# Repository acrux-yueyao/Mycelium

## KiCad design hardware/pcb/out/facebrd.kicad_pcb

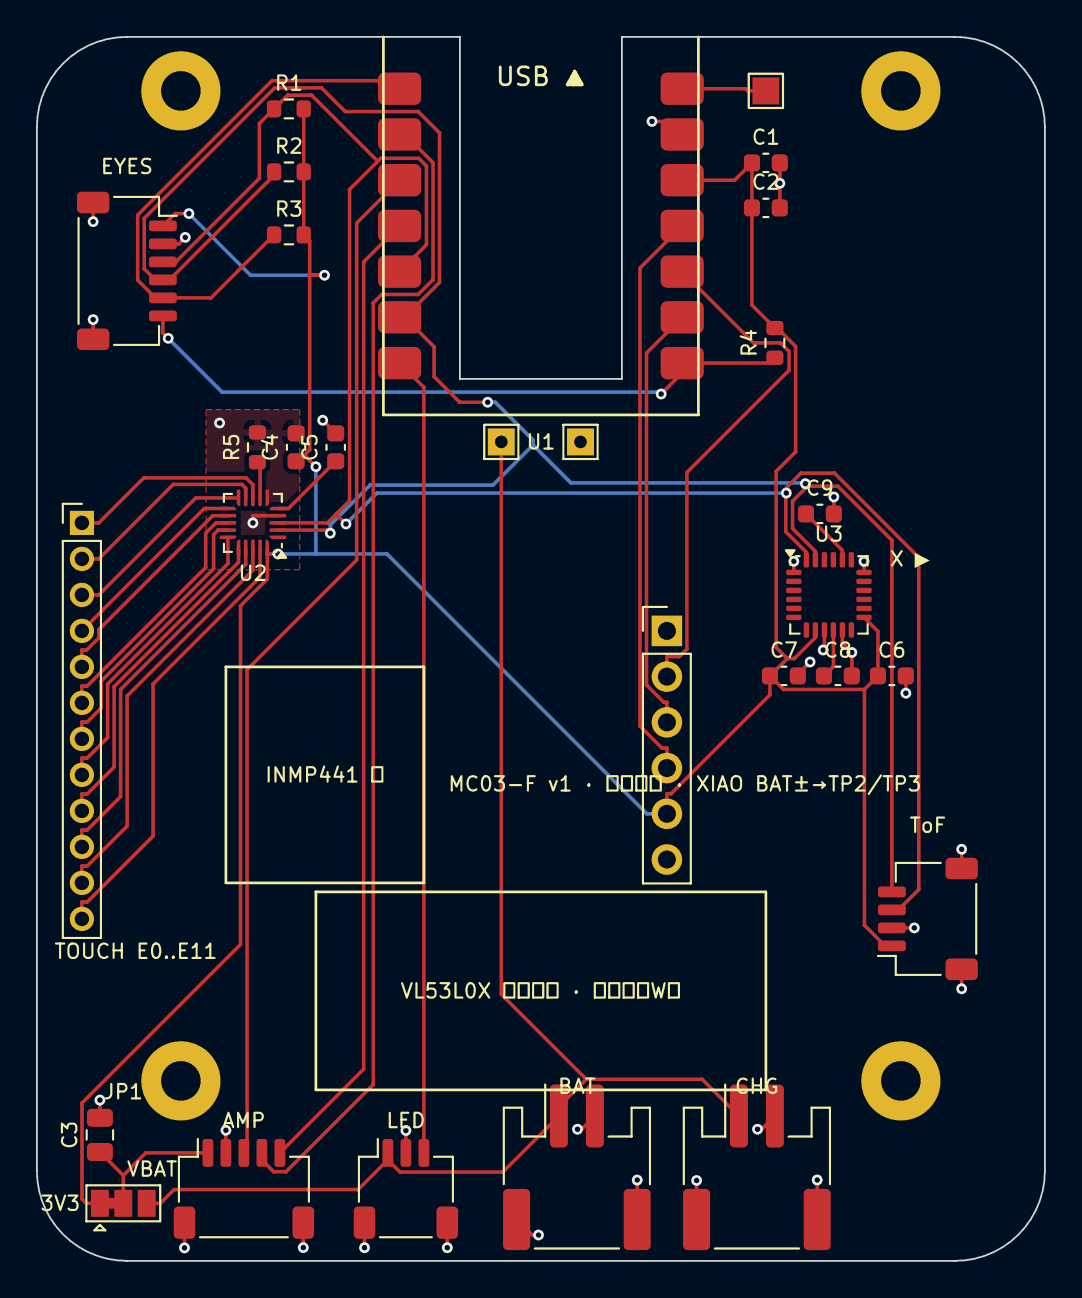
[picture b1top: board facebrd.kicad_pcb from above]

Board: 2 copper layers, 56.0 x 68.0 mm, 33 parts (0 on the bottom side), 32 nets.

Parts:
C1: 10uF; C_0603_1608Metric
C2, C4, C5, C6, C8: 100nF; C_0603_1608Metric
C3: 22uF; C_0805_2012Metric
C7: 10nF; C_0603_1608Metric
C9: 2.2nF; C_0603_1608Metric
H1, H2, H3, H4: M2; MountingHole_2.2mm_M2_Pad
J1: ToF 4P; JST_SH_SM04B-SRSS-TB_1x04-1MP_P1.00mm_Horizontal
J2: MIC pads; PinHeader_1x06_P2.54mm_Vertical
J3: EYES 6P; JST_SH_SM06B-SRSS-TB_1x06-1MP_P1.00mm_Horizontal
J4: BAT; JST_PH_S2B-PH-SM4-TB_1x02-1MP_P2.00mm_Horizontal
J5: LED 3P; JST_SH_SM03B-SRSS-TB_1x03-1MP_P1.00mm_Horizontal
J6: AMP 5P; JST_SH_SM05B-SRSS-TB_1x05-1MP_P1.00mm_Horizontal
J7: TOUCH pads; PinHeader_1x12_P2.00mm_Vertical
J8: CHG; JST_PH_S2B-PH-SM4-TB_1x02-1MP_P2.00mm_Horizontal
JP1: AMP_VIN sel; SolderJumper-3_P1.3mm_Bridged12_Pad1.0x1.5mm
R1, R2, R3, R4: 4.7k; R_0603_1608Metric
R5: 75k; R_0603_1608Metric
TP1: VBUS; TestPoint_Pad_1.5x1.5mm
TP2: BAT+; TestPoint_THTPad_1.5x1.5mm_Drill0.7mm
TP3: BAT-; TestPoint_THTPad_1.5x1.5mm_Drill0.7mm
U1: XIAO-ESP32S3; XIAO-ESP32S3_SMD
U2: MPR121QR2; UQFN-20_3x3mm_P0.4mm
U3: MPU-6050; InvenSense_QFN-24_4x4mm_P0.5mm

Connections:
3V3: C1.1, C2.1, C4.1, C6.1, C7.1, J1.1, J2.5, J3.1, JP1.1, R1.2, R2.2, R3.2, R4.2, U1.12, U2.20, U3.8, U3.13
AMP_VIN: C3.1, J6.1, JP1.2
CPOUT: C9.1, U3.20
ELE0: J7.1, U2.8
ELE1: J7.2, U2.9
ELE2: J7.3, U2.10
ELE3: J7.4, U2.11
ELE4: J7.5, U2.12
ELE5: J7.6, U2.13
ELE6: J7.7, U2.14
ELE7: J7.8, U2.15
ELE8: J7.9, U2.16
ELE9: J7.10, U2.17
ELE10: J7.11, U2.18
ELE11: J7.12, U2.19
GND: C1.2, C2.2, C3.2, C4.2, C5.2, C6.2, C7.2, C8.2, C9.2, H1.1, H2.1, H3.1, H4.1, J1.2, J1.MP, J2.1, J2.6, J3.2, J3.MP, J4.2, J4.MP, J5.2, J5.MP, J6.2, J6.MP, J8.2, J8.MP, R5.2, TP3.1, U1.13, U2.4, U2.6, U3.1, U3.9, U3.11, U3.18
I2S_BCLK: J6.3, U1.3
I2S_DIN: J6.5, U1.4
I2S_LRC: J6.4, U1.2
LED_DIN: J5.3, U1.7
MIC_SCK: J2.3, U1.9
MIC_SD: J2.4, U1.11
MIC_WS: J2.2, U1.10
REGOUT: C8.1, U3.10
REXT: R5.1, U2.7
SCL0: J1.4, J3.4, R2.1, U1.6, U2.2, U3.23
SCL1: J3.6, R4.1, U1.8
SDA0: J1.3, J3.3, R1.1, U1.5, U2.3, U3.24
SDA1: J3.5, R3.1, U1.1
VBAT: J4.1, J5.1, J8.1, JP1.3, TP2.1
VBUS: TP1.1, U1.14
VREG: C5.1, U2.5

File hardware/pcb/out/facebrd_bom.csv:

Comment,Designator,Footprint,LCSC Part #
MPR121QR2,U2,UQFN-20_3x3mm_P0.4mm,C91322
MPU-6050,U3,InvenSense_QFN-24_4x4mm_P0.5mm,C24112
10uF,C1,C_0603_1608Metric,C19702
100nF,"C2,C4,C5,C6,C8",C_0603_1608Metric,C14663
22uF,C3,C_0805_2012Metric,C45783
75k,R5,R_0603_1608Metric,C18671
10nF,C7,C_0603_1608Metric,C57112
2.2nF,C9,C_0603_1608Metric,C1604
4.7k,"R1,R2,R3,R4",R_0603_1608Metric,C23162
ToF 4P,J1,JST_SH_SM04B-SRSS-TB_1x04-1MP_P1.00mm_Horizontal,C51940130
EYES 6P,J3,JST_SH_SM06B-SRSS-TB_1x06-1MP_P1.00mm_Horizontal,C56123098
AMP 5P,J6,JST_SH_SM05B-SRSS-TB_1x05-1MP_P1.00mm_Horizontal,C136657
LED 3P,J5,JST_SH_SM03B-SRSS-TB_1x03-1MP_P1.00mm_Horizontal,C53055319
BAT,J4,JST_PH_S2B-PH-SM4-TB_1x02-1MP_P2.00mm_Horizontal,C54582899
CHG,J8,JST_PH_S2B-PH-SM4-TB_1x02-1MP_P2.00mm_Horizontal,C54582899

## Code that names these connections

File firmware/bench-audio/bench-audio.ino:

/*
 * MC-01 面包板验货 · 阶段2:声音链
 *
 * 验两件事:
 *   1) MAX98357A + 3020 喇叭能出声(播一段音阶)
 *   2) INMP441 麦克风能收声(串口打条形音量表)
 *
 * 接线见 hardware/bench_circuit.png 下半张:
 *   麦   SCK→G14  WS→G15  SD→G32   VDD→3V3  GND→GND  L/R→GND(必须)
 *   功放 BCLK→G26 LRC→G25 DIN→G27  VIN→3V3  GND→GND  GAIN/SD 悬空
 *
 * 串口 115200,按键:
 *   t  播一次音阶(do re mi fa so)
 *   b  播一声"哔"
 *   m  切换麦克风音量表(默认开)
 */
#include <driver/i2s.h>
#include <math.h>

// 板型自动识别:XIAO ESP32S3 = 合板脚位(J2/J6);WROOM = 面包板脚位
#if defined(ARDUINO_XIAO_ESP32S3)
constexpr int MIC_SCK = D8, MIC_WS = D9, MIC_SD = D10;
constexpr int AMP_BCLK = D2, AMP_LRC = D1, AMP_DIN = D3;
#else
constexpr int MIC_SCK = 14, MIC_WS = 15, MIC_SD = 32;
constexpr int AMP_BCLK = 26, AMP_LRC = 25, AMP_DIN = 27;
#endif

constexpr int SAMPLE_RATE = 16000;
constexpr i2s_port_t PORT_AMP = I2S_NUM_0;
constexpr i2s_port_t PORT_MIC = I2S_NUM_1;

bool meterOn = true;

void setupAmp() {
  i2s_config_t cfg = {};
  cfg.mode = (i2s_mode_t)(I2S_MODE_MASTER | I2S_MODE_TX);
  cfg.sample_rate = SAMPLE_RATE;
  cfg.bits_per_sample = I2S_BITS_PER_SAMPLE_16BIT;
  cfg.channel_format = I2S_CHANNEL_FMT_ONLY_LEFT;
  cfg.communication_format = I2S_COMM_FORMAT_STAND_I2S;
  cfg.intr_alloc_flags = 0;
  cfg.dma_buf_count = 8;
  cfg.dma_buf_len = 256;
  cfg.use_apll = false;
  i2s_pin_config_t pins = {};
  pins.mck_io_num = I2S_PIN_NO_CHANGE;
  pins.bck_io_num = AMP_BCLK;
  pins.ws_io_num = AMP_LRC;
  pins.data_out_num = AMP_DIN;
  pins.data_in_num = I2S_PIN_NO_CHANGE;
  i2s_driver_install(PORT_AMP, &cfg, 0, NULL);
  i2s_set_pin(PORT_AMP, &pins);
}

void setupMic() {
  i2s_config_t cfg = {};
  cfg.mode = (i2s_mode_t)(I2S_MODE_MASTER | I2S_MODE_RX);
  cfg.sample_rate = SAMPLE_RATE;
  cfg.bits_per_sample = I2S_BITS_PER_SAMPLE_32BIT;   // INMP441 送 24bit/32bit 帧
  cfg.channel_format = I2S_CHANNEL_FMT_ONLY_LEFT;    // L/R 接地 = 左声道
  cfg.communication_format = I2S_COMM_FORMAT_STAND_I2S;
  cfg.intr_alloc_flags = 0;
  cfg.dma_buf_count = 4;
  cfg.dma_buf_len = 256;
  cfg.use_apll = false;
  i2s_pin_config_t pins = {};
  pins.mck_io_num = I2S_PIN_NO_CHANGE;
  pins.bck_io_num = MIC_SCK;
  pins.ws_io_num = MIC_WS;
  pins.data_out_num = I2S_PIN_NO_CHANGE;
  pins.data_in_num = MIC_SD;
  i2s_driver_install(PORT_MIC, &cfg, 0, NULL);
  i2s_set_pin(PORT_MIC, &pins);
}

// 播一个正弦音,freq 赫兹,ms 毫秒,vol 0..1
void tone(float freq, int ms, float vol = 0.35f) {
  const int N = 256;
  int16_t buf[N];
  static float phase = 0;
  float step = 2.0f * PI * freq / SAMPLE_RATE;
  int total = SAMPLE_RATE * ms / 1000;
  size_t wrote;
  while (total > 0) {
    int n = min(N, total);
    for (int i = 0; i < n; i++) {
      // 两端做淡入淡出,避免"啪"的爆音
      buf[i] = (int16_t)(sinf(phase) * 26000 * vol);
      phase += step;
      if (phase > 2 * PI) phase -= 2 * PI;
    }
    i2s_write(PORT_AMP, buf, n * sizeof(int16_t), &wrote, portMAX_DELAY);
    total -= n;
  }
  // 收尾清零,喇叭不带直流
  memset(buf, 0, sizeof(buf));
  i2s_write(PORT_AMP, buf, sizeof(buf), &wrote, portMAX_DELAY);
}

void scale() {
  const float notes[] = {262, 294, 330, 349, 392};   // do re mi fa so
  for (float f : notes) { tone(f, 220); delay(40); }
}

void setup() {
  Serial.begin(115200);
  delay(400);
  Serial.println("\n=== MC-01 声音链验货 ===");
  setupAmp();
  setupMic();
  Serial.println("功放:播放音阶 —— 听喇叭");
  scale();
  Serial.println("麦克风:对着麦说话/吹气,下面的条应该变长");
  Serial.println("按键: t=音阶  b=哔  m=开关音量表");
}

void loop() {
  if (Serial.available()) {
    char c = Serial.read();
    if (c == 't') { Serial.println("[播音阶]"); scale(); }
    else if (c == 'b') { Serial.println("[哔]"); tone(880, 150); }
    else if (c == 'm') { meterOn = !meterOn; Serial.printf("[音量表 %s]\n", meterOn ? "开" : "关"); }
  }

  if (!meterOn) { delay(50); return; }

  int32_t samples[256];
  size_t got = 0;
  i2s_read(PORT_MIC, samples, sizeof(samples), &got, 100 / portTICK_PERIOD_MS);
  int n = got / sizeof(int32_t);
  if (n == 0) {
    Serial.println("麦无数据 —— 查 SD/SCK/WS 接线,L/R 是否接地");
    delay(500);
    return;
  }
  long peak = 0;
  for (int i = 0; i < n; i++) {
    long v = samples[i] >> 14;              // 32bit 帧里取有效位
    if (labs(v) > peak) peak = labs(v);
  }
  int bars = constrain((int)(peak / 400), 0, 40);
  Serial.printf("%6ld |", peak);
  for (int i = 0; i < bars; i++) Serial.print('#');
  Serial.println();
  delay(120);
}
